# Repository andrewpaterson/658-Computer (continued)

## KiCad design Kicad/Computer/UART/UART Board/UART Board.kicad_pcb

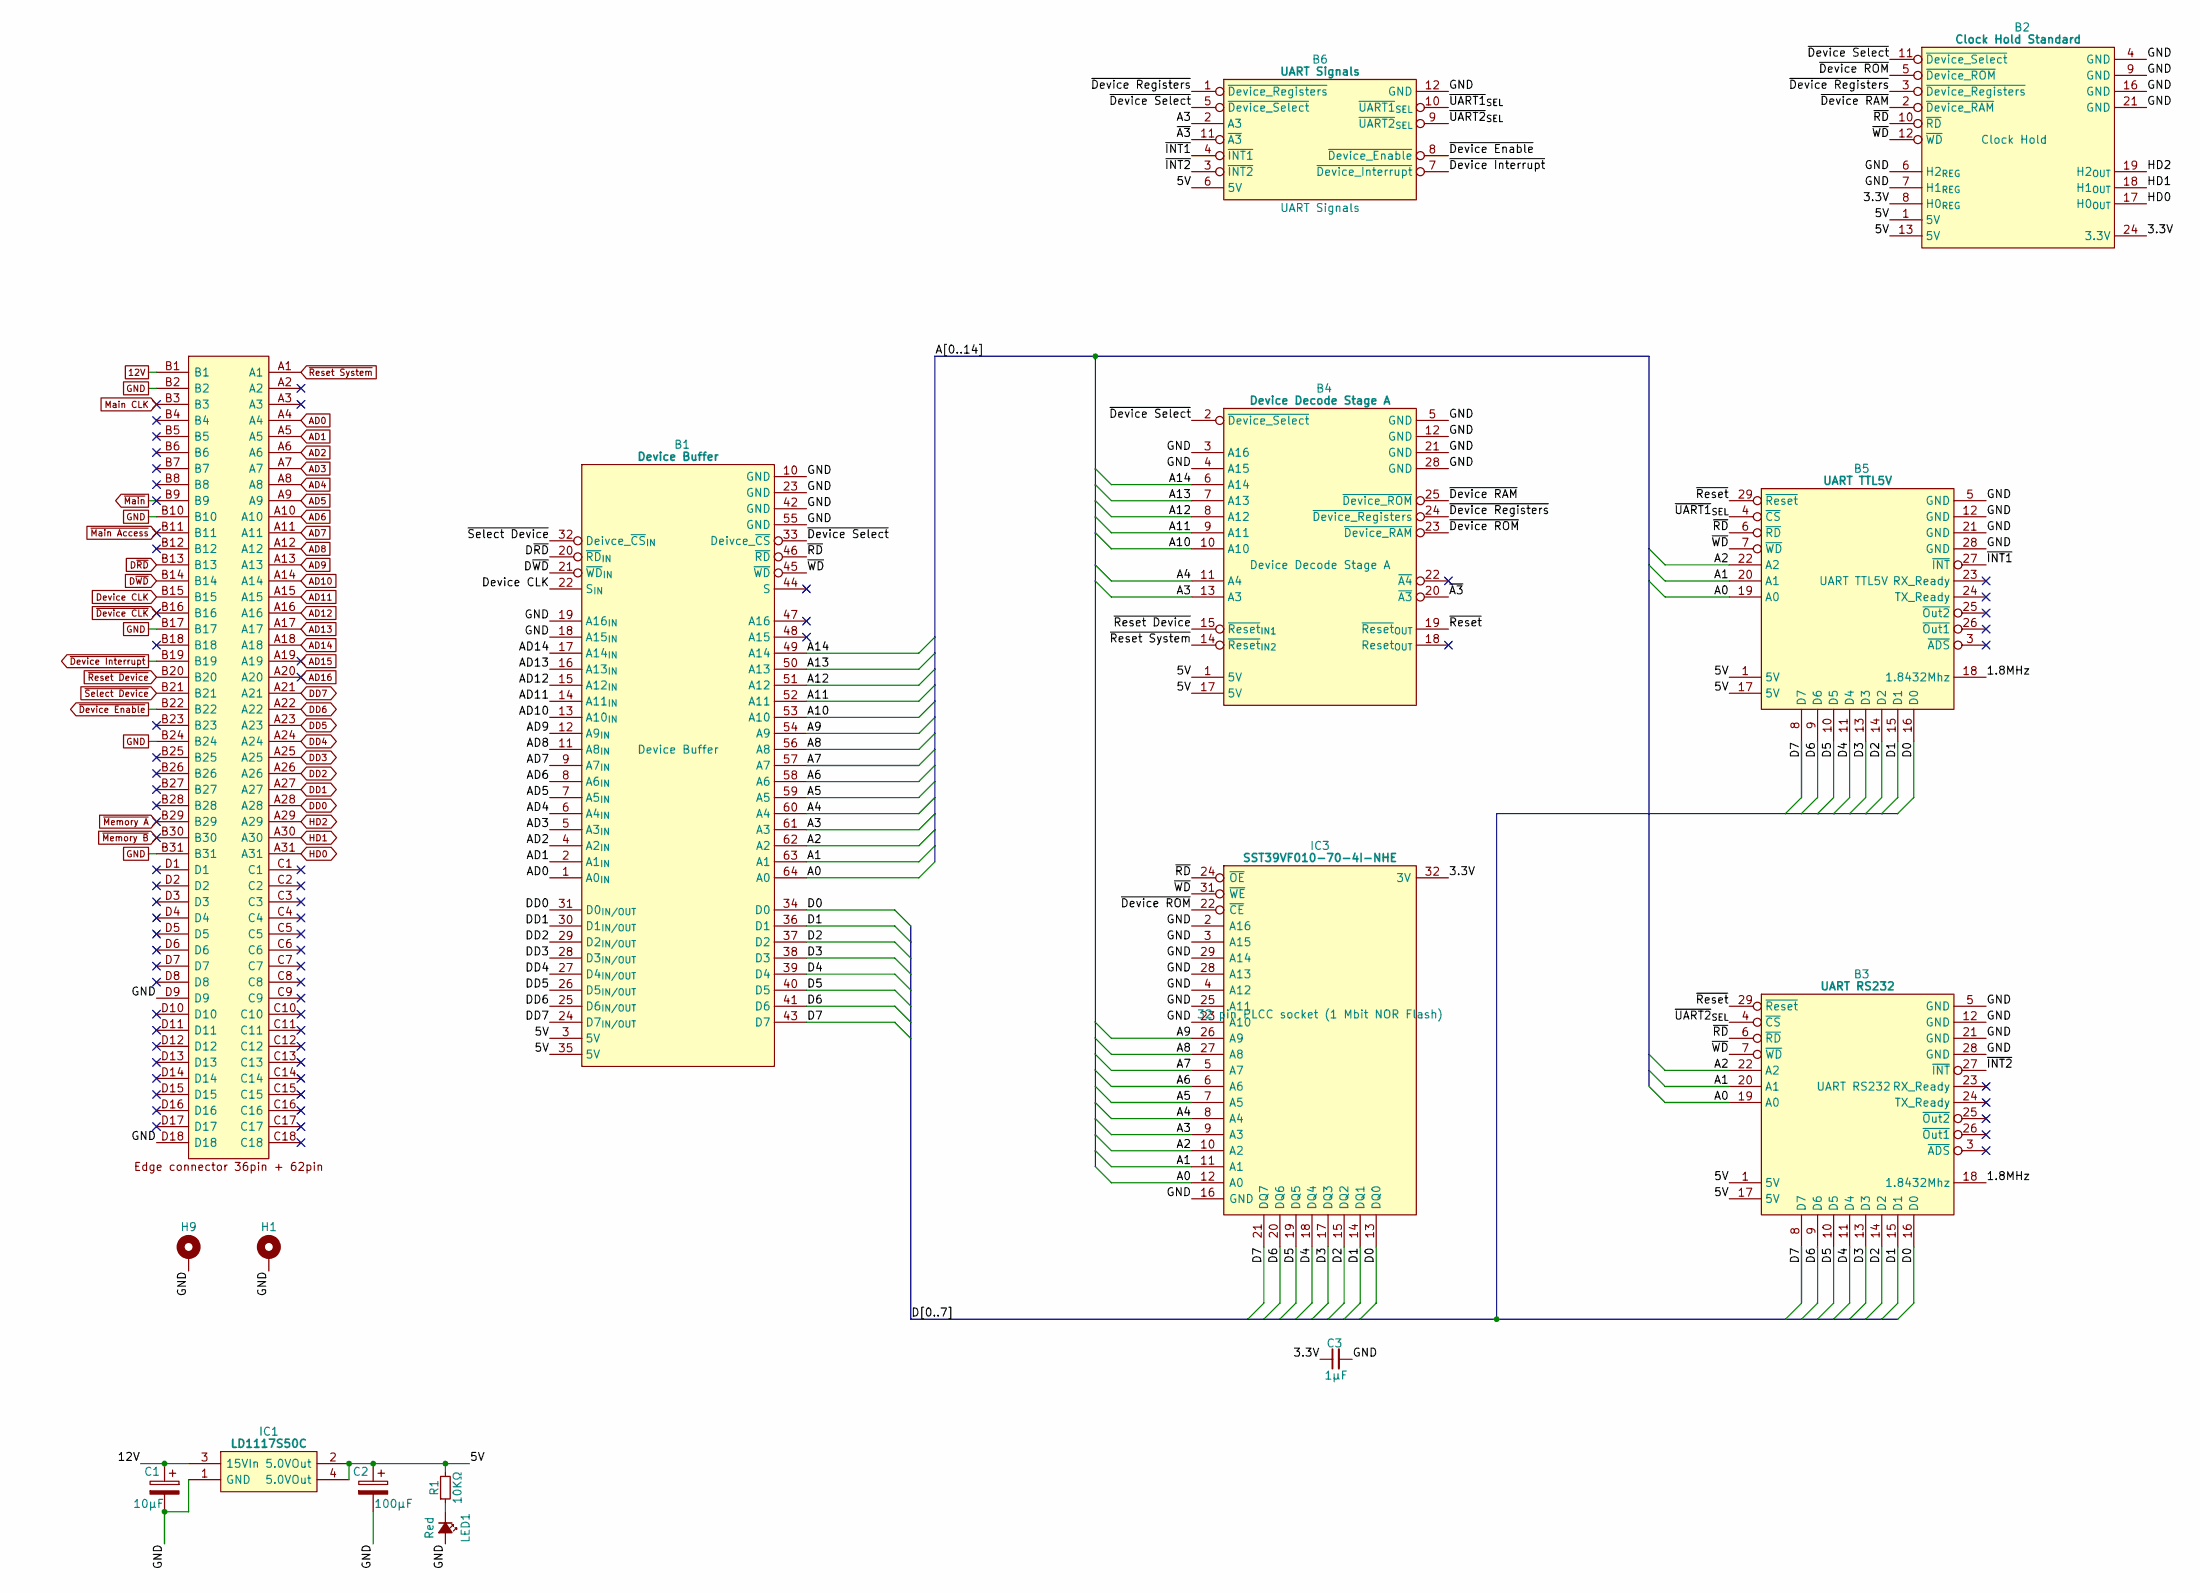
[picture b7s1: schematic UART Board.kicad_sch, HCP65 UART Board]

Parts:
B1: Device Buffer; HCP65_Device_Buffer
B2: Clock Hold Standard; HCP65_Clock_Hold_Standard
B3: UART RS232; HCP65_RS232_UART
B4: Device Decode Stage A; HCP65_Device_Decode_Stage_A
B5: UART TTL5V; HCP65_TTL5V_UART
B6: UART Signals; HCP65_UART_Signals
C1: 10μF; CP_Radial_D4.0mm_P2.00mm
C2: 100μF; CP_Radial_D4.0mm_P2.00mm
C3: 1μF; C_0805
H1, H9: MountingHole_Pad; HCP65_MountingHole_M3_
IC1: LD1117S50C; LD1117S33C; Manufacturer_Part_Number LD1117S50C
IC3: SST39VF010-70-4I-NHE; 5408803224008; Manufacturer_Part_Number SST39VF010-70-4I-NHE
J5: 395-098-520-350; 98pin Edge Connector; Manufacturer_Part_Number 395-098-520-350; Mouser Part Number 587-395-098-520-350
LED1: Red; LED_D5.0mm
R1: 10KΩ; R_0805

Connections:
12V: C1.1, IC1.3 (15VIn), J5.B1
/3.3V: B2.8 (H0_{REG}), B2.24 (3.3V), C3.1, IC3.32 (3V)
/5V: B1.3 (5V), B1.35 (5V), B2.1 (5V), B2.13 (5V), B3.1 (5V), B3.17 (5V), B4.1 (5V), B4.17 (5V), B5.1 (5V), B5.17 (5V), B6.6 (5V), C2.1, IC1.2 (5.0VOut), IC1.4 (5.0VOut), R1.2
/A0: B1.64 (A0), B3.19 (A0), B5.19 (A0), IC3.12 (A0)
/A1: B1.63 (A1), B3.20 (A1), B5.20 (A1), IC3.11 (A1)
/A2: B1.62 (A2), B3.22 (A2), B5.22 (A2), IC3.10 (A2)
/A3: B1.61 (A3), B4.13 (A3), B6.2 (A3), IC3.9 (A3)
/A4: B1.60 (A4), B4.11 (A4), IC3.8 (A4)
/A5: B1.59 (A5), IC3.7 (A5)
/A6: B1.58 (A6), IC3.6 (A6)
/A7: B1.57 (A7), IC3.5 (A7)
/A8: B1.56 (A8), IC3.27 (A8)
/A9: B1.54 (A9), IC3.26 (A9)
/A10: B1.53 (A10), B4.10 (A10)
/A11: B1.52 (A11), B4.9 (A11)
/A12: B1.51 (A12), B4.8 (A12)
/A13: B1.50 (A13), B4.7 (A13)
/A14: B1.49 (A14), B4.6 (A14)
/D0: B1.34 (D0), B3.16 (D0), B5.16 (D0), IC3.13 (DQ0)
/D1: B1.36 (D1), B3.15 (D1), B5.15 (D1), IC3.14 (DQ1)
/D2: B1.37 (D2), B3.14 (D2), B5.14 (D2), IC3.15 (DQ2)
/D3: B1.38 (D3), B3.13 (D3), B5.13 (D3), IC3.17 (DQ3)
/D4: B1.39 (D4), B3.11 (D4), B5.11 (D4), IC3.18 (DQ4)
/D5: B1.40 (D5), B3.10 (D5), B5.10 (D5), IC3.19 (DQ5)
/D6: B1.41 (D6), B3.9 (D6), B5.9 (D6), IC3.20 (DQ6)
/D7: B1.43 (D7), B3.8 (D7), B5.8 (D7), IC3.21 (DQ7)
/~A3: B4.20 (~A3), B6.11 (~A3)
/~Device RAM: B2.2 (~Device_RAM), B4.25 (~Device_ROM)
/~Device ROM: B2.5 (~Device_ROM), B4.23 (~Device_RAM), IC3.22 (~CE)
/~Device Registers: B2.3 (~Device_Registers), B4.24 (~Device_Registers), B6.1 (~Device_Registers)
/~Device Select: B1.33 (Deivce_~CS), B2.11 (~Device_Select), B4.2 (~Device_Select), B6.5 (~Device_Select)
/~INT1: B5.27 (~INT), B6.4 (~INT1)
/~INT2: B3.27 (~INT), B6.3 (~INT2)
/~RD: B1.46 (~RD), B2.10 (~RD), B3.6 (~RD), B5.6 (~RD), IC3.24 (~OE)
/~Reset: B3.29 (~Reset), B4.19 (~Reset_{OUT}), B5.29 (~Reset)
/~UART1_{SEL}: B5.4 (~CS), B6.10 (~UART1_{SEL})
/~UART2_{SEL}: B3.4 (~CS), B6.9 (~UART2_{SEL})
/~WD: B1.45 (~WD), B2.12 (~WD), B3.7 (~WD), B5.7 (~WD), IC3.31 (~WE)
AD0: B1.1 (A0_{IN}), J5.A4
AD1: B1.2 (A1_{IN}), J5.A5
AD2: B1.4 (A2_{IN}), J5.A6
AD3: B1.5 (A3_{IN}), J5.A7
AD4: B1.6 (A4_{IN}), J5.A8
AD5: B1.7 (A5_{IN}), J5.A9
AD6: B1.8 (A6_{IN}), J5.A10
AD7: B1.9 (A7_{IN}), J5.A11
AD8: B1.11 (A8_{IN}), J5.A12
AD9: B1.12 (A9_{IN}), J5.A13
AD10: B1.13 (A10_{IN}), J5.A14
AD11: B1.14 (A11_{IN}), J5.A15
AD12: B1.15 (A12_{IN}), J5.A16
AD13: B1.16 (A13_{IN}), J5.A17
AD14: B1.17 (A14_{IN}), J5.A18
AD15: J5.A19
AD16: J5.A20
DD0: B1.31 (D0_{IN/OUT}), J5.A28
DD1: B1.30 (D1_{IN/OUT}), J5.A27
DD2: B1.29 (D2_{IN/OUT}), J5.A26
DD3: B1.28 (D3_{IN/OUT}), J5.A25
DD4: B1.27 (D4_{IN/OUT}), J5.A24
DD5: B1.26 (D5_{IN/OUT}), J5.A23
DD6: B1.25 (D6_{IN/OUT}), J5.A22
DD7: B1.24 (D7_{IN/OUT}), J5.A21
Device CLK: B1.22 (S_{IN}), J5.B15
D~RD: B1.20 (~RD_{IN}), J5.B13
D~WD: B1.21 (~WD_{IN}), J5.B14
GND: B1.10 (GND), B1.18 (A15_{IN}), B1.19 (A16_{IN}), B1.23 (GND), B1.42 (GND), B1.55 (GND), B2.4 (GND), B2.6 (H2_{REG}), B2.7 (H1_{REG}), B2.9 (GND), B2.16 (GND), B2.21 (GND), B3.5 (GND), B3.12 (GND), B3.21 (GND), B3.28 (GND), B4.3 (A16), B4.4 (A15), B4.5 (GND), B4.12 (GND), B4.21 (GND), B4.28 (GND), B5.5 (GND), B5.12 (GND), B5.21 (GND), B5.28 (GND), B6.12 (GND), C1.2, C2.2, C3.2, H1.1 (GND), H9.1 (GND), IC1.1 (GND), IC3.2 (A16), IC3.3 (A15), IC3.4 (A12), IC3.16 (GND), IC3.23 (A10), IC3.25 (A11), IC3.28 (A13), IC3.29 (A14), J5.B2, J5.B10, J5.B17, J5.B24, J5.B31, J5.D9, J5.D18, LED1.2 (A)
HD0: B2.17 (H0_{OUT}), J5.A31
HD1: B2.18 (H1_{OUT}), J5.A30
HD2: B2.19 (H2_{OUT}), J5.A29
Main CLK: J5.B3
unnamed: LED1.1 (K), R1.1
~Device CLK: J5.B16
~Device Enable: B6.8 (~Device_Enable), J5.B22
~Device Interrupt: B6.7 (~Device_Interrupt), J5.B19
~Main Access: J5.B11
~Main: J5.B9
~Memory A: J5.B29
~Memory B: J5.B30
~Reset Device: B4.15 (~Reset_{IN1}), J5.B20
~Reset System: B4.14 (~Reset_{IN2}), J5.A1
~Select Device: B1.32 (Deivce_~CS_{IN}), J5.B21

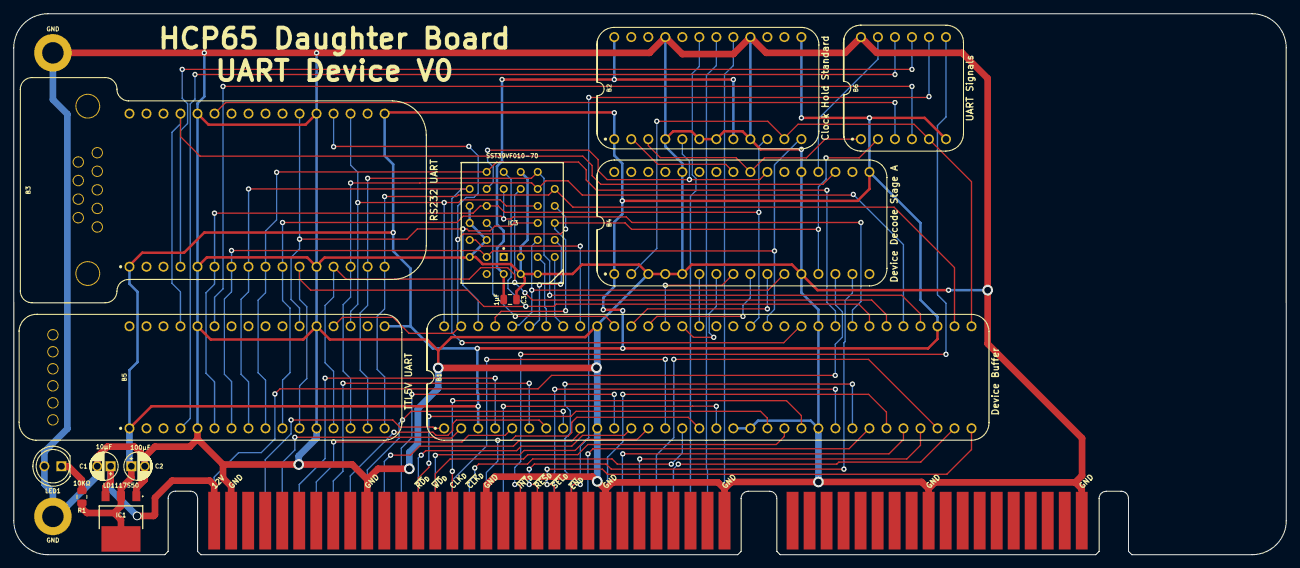
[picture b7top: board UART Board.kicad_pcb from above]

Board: 2 copper layers, 190.0 x 80.8 mm, 16 parts (0 on the bottom side), 74 nets.
